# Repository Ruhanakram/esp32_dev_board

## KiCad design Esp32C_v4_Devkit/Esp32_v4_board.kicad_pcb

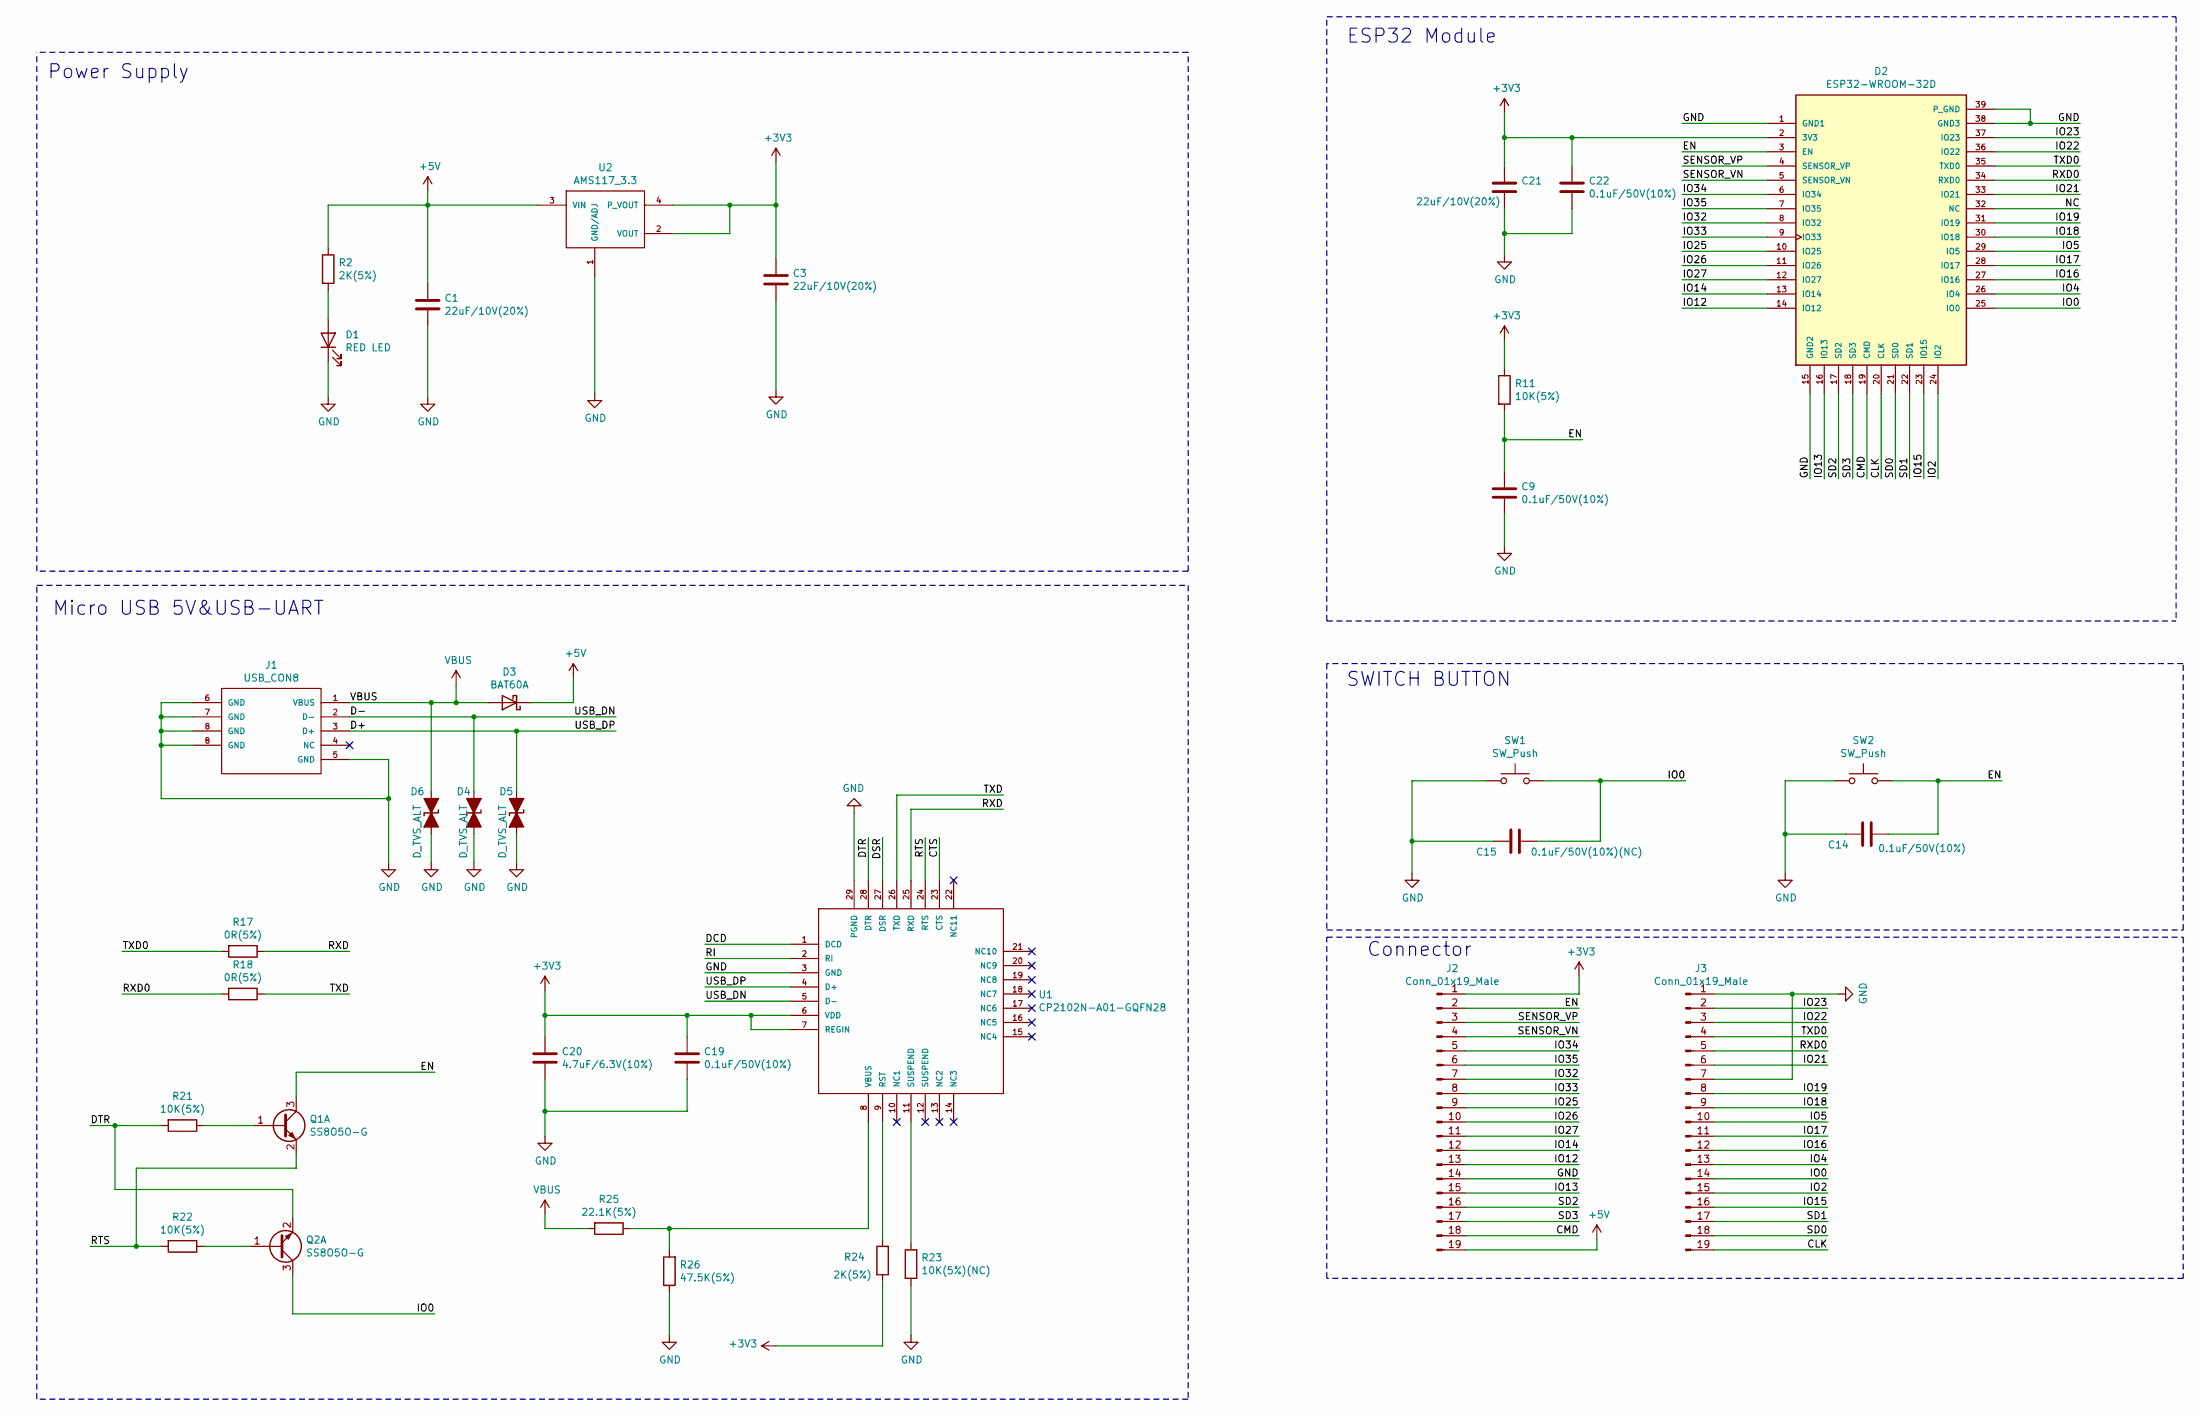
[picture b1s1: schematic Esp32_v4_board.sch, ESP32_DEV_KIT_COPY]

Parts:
C1, C3, C21: 22uF/10V(20%); C_0603_1608Metric
C9, C14, C19, C22: 0.1uF/50V(10%); C_0402_1005Metric
C15: 0.1uF/50V(10%)(NC); C_0603_1608Metric
C20: 4.7uF/6.3V(10%); C_0402_1005Metric
D1: RED LED; LED_0603_1608Metric
D2: ESP32-WROOM-32D; esp32_wroom_32e; PARTREV 1.9
D3: BAT60A; D_SOD-323
D4, D5, D6: D_TVS_ALT; D_SOD-523
J1: USB_CON8; Micro_usb_connector_4_THT_pads
J2, J3: Conn_01x19_Male; PinHeader_1x19_P2.54mm_Vertical
Q1, Q2: SS8O5O-G; TSOT-23
R2, R24: 2K(5%); R_0402_1005Metric
R11, R21, R22: 10K(5%); R_0402_1005Metric
R17, R18: 0R(5%); R_0402_1005Metric
R23: 10K(5%)(NC); R_0402_1005Metric
R25: 22.1K(5%); R_0402_1005Metric
R26: 47.5K(5%); R_0402_1005Metric
SW1, SW2: SW_Push; SW_SPST_B3U-1000P
U1: CP2102N-A01-GQFN28; QFN-28-1EP_5x5mm_P0.5mm_EP3.35x3.35mm
U2: AMS117_3.3; SOT-223

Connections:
+3V3: C3.1, C19.1, C20.1, C21.1, C22.1, D2.2 (3V3), J2.1, R11.1, R24.1, U1.6 (VDD), U1.7 (REGIN), U2.2 (VOUT), U2.4 (P_VOUT)
+5V: C1.1, D3.1 (K), J2.19, R2.1, U2.3 (VIN)
/CLK: D2.20 (CLK), J3.19
/CMD: D2.19 (CMD), J2.18
/CTS: U1.23 (CTS)
/D+: D5.2 (A2), J1.3 (D+), U1.4 (D+)
/D-: D4.2 (A2), J1.2 (D-), U1.5 (D-)
/DCD: U1.1 (DCD)
/DSR: U1.27 (DSR)
/DTR: Q2.2 (E1), R21.2, U1.28 (DTR)
/EN: C9.1, C14.2, D2.3 (EN), J2.2, Q1.3 (C1), R11.2, SW2.2
/IO0: C15.2, D2.25 (IO0), J3.14, Q2.3 (C1), SW1.2
/IO2: D2.24 (IO2), J3.15
/IO4: D2.26 (IO4), J3.13
/IO5: D2.29 (IO5), J3.10
/IO12: D2.14 (IO12), J2.13
/IO13: D2.16 (IO13), J2.15
/IO14: D2.13 (IO14), J2.12
/IO15: D2.23 (IO15), J3.16
/IO16: D2.27 (IO16), J3.12
/IO17: D2.28 (IO17), J3.11
/IO18: D2.30 (IO18), J3.9
/IO19: D2.31 (IO19), J3.8
/IO21: D2.33 (IO21), J3.6
/IO22: D2.36 (IO22), J3.3
/IO23: D2.37 (IO23), J3.2
/IO25: D2.10 (IO25), J2.9
/IO26: D2.11 (IO26), J2.10
/IO27: D2.12 (IO27), J2.11
/IO32: D2.8 (IO32), J2.7
/IO33: D2.9 (IO33), J2.8
/IO34: D2.6 (IO34), J2.5
/IO35: D2.7 (IO35), J2.6
/NC: D2.32 (NC)
/RI: U1.2 (RI)
/RTS: Q1.2 (E1), R22.2, U1.24 (RTS)
/RXD: R17.1, U1.25 (RXD)
/RXD0: D2.34 (RXD0), J3.5, R18.2
/SD0: D2.21 (SD0), J3.18
/SD1: D2.22 (SD1), J3.17
/SD2: D2.17 (SD2), J2.16
/SD3: D2.18 (SD3), J2.17
/SENSOR_VN: D2.5 (SENSOR_VN), J2.4
/SENSOR_VP: D2.4 (SENSOR_VP), J2.3
/TXD: R18.1, U1.26 (TXD)
/TXD0: D2.35 (TXD0), J3.4, R17.2
GND: C1.2, C3.2, C9.2, C14.1, C15.1, C19.2, C20.2, C21.2, C22.2, D1.1 (K), D2.1 (GND1), D2.15 (GND2), D2.38 (GND3), D2.39 (P_GND), D4.1 (A1), D5.1 (A1), D6.1 (A1), J1.5 (GND), J1.6 (GND), J1.7 (GND), J1.8 (GND), J2.14, J3.1, J3.7, R23.1, R26.1, SW1.1, SW2.1, U1.3 (GND), U1.29 (PGND), U2.1 (GND/ADJ)
unnamed: D1.2 (A), R2.2
unnamed: Q1.1 (B1), R21.1
unnamed: Q2.1 (B1), R22.1
unnamed: R23.2, U1.11 (SUSPEND)
unnamed: R24.2, U1.9 (RST)
unnamed: R25.1, R26.2, U1.8 (VBUS)
VBUS: D3.2 (A), D6.2 (A2), J1.1 (VBUS), R25.2

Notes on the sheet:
Power Supply
Micro USB 5V&USB-UART
ESP32 Module
SWITCH BUTTON
Connector

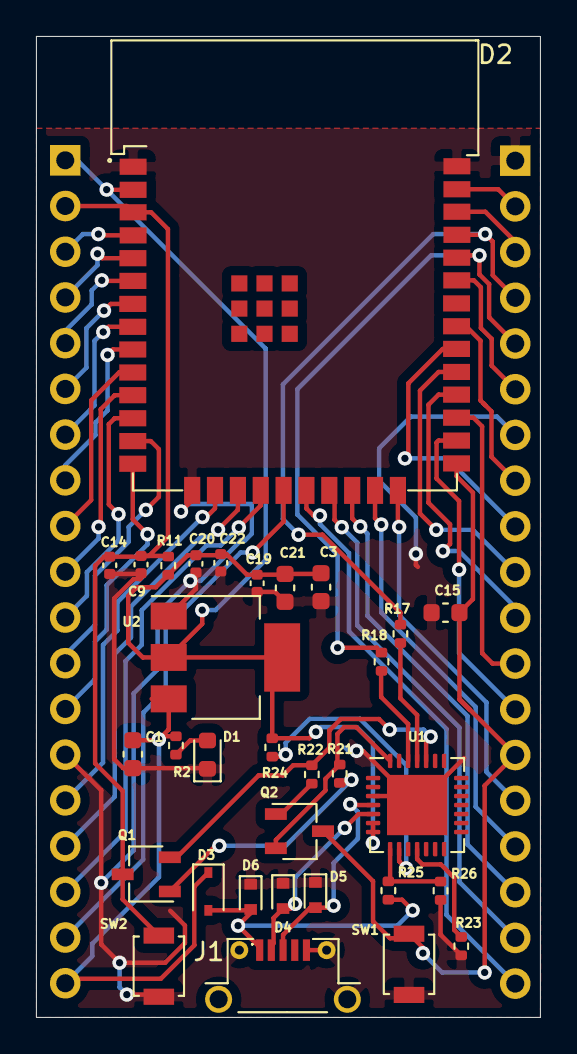
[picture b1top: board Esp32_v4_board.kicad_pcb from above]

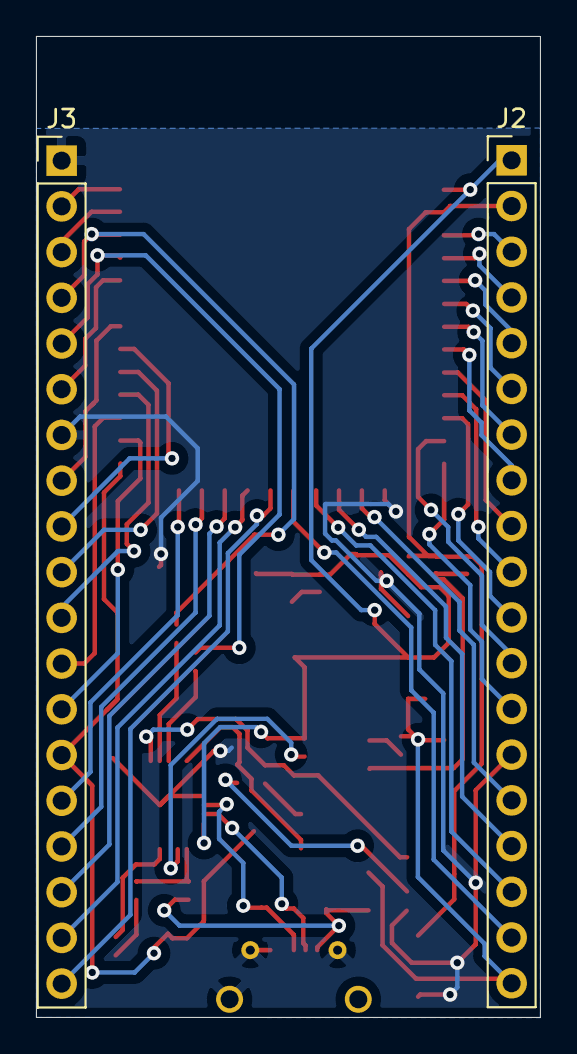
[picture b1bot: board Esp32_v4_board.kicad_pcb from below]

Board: 2 copper layers, 28.0 x 54.5 mm, 34 parts (2 on the bottom side), 49 nets.

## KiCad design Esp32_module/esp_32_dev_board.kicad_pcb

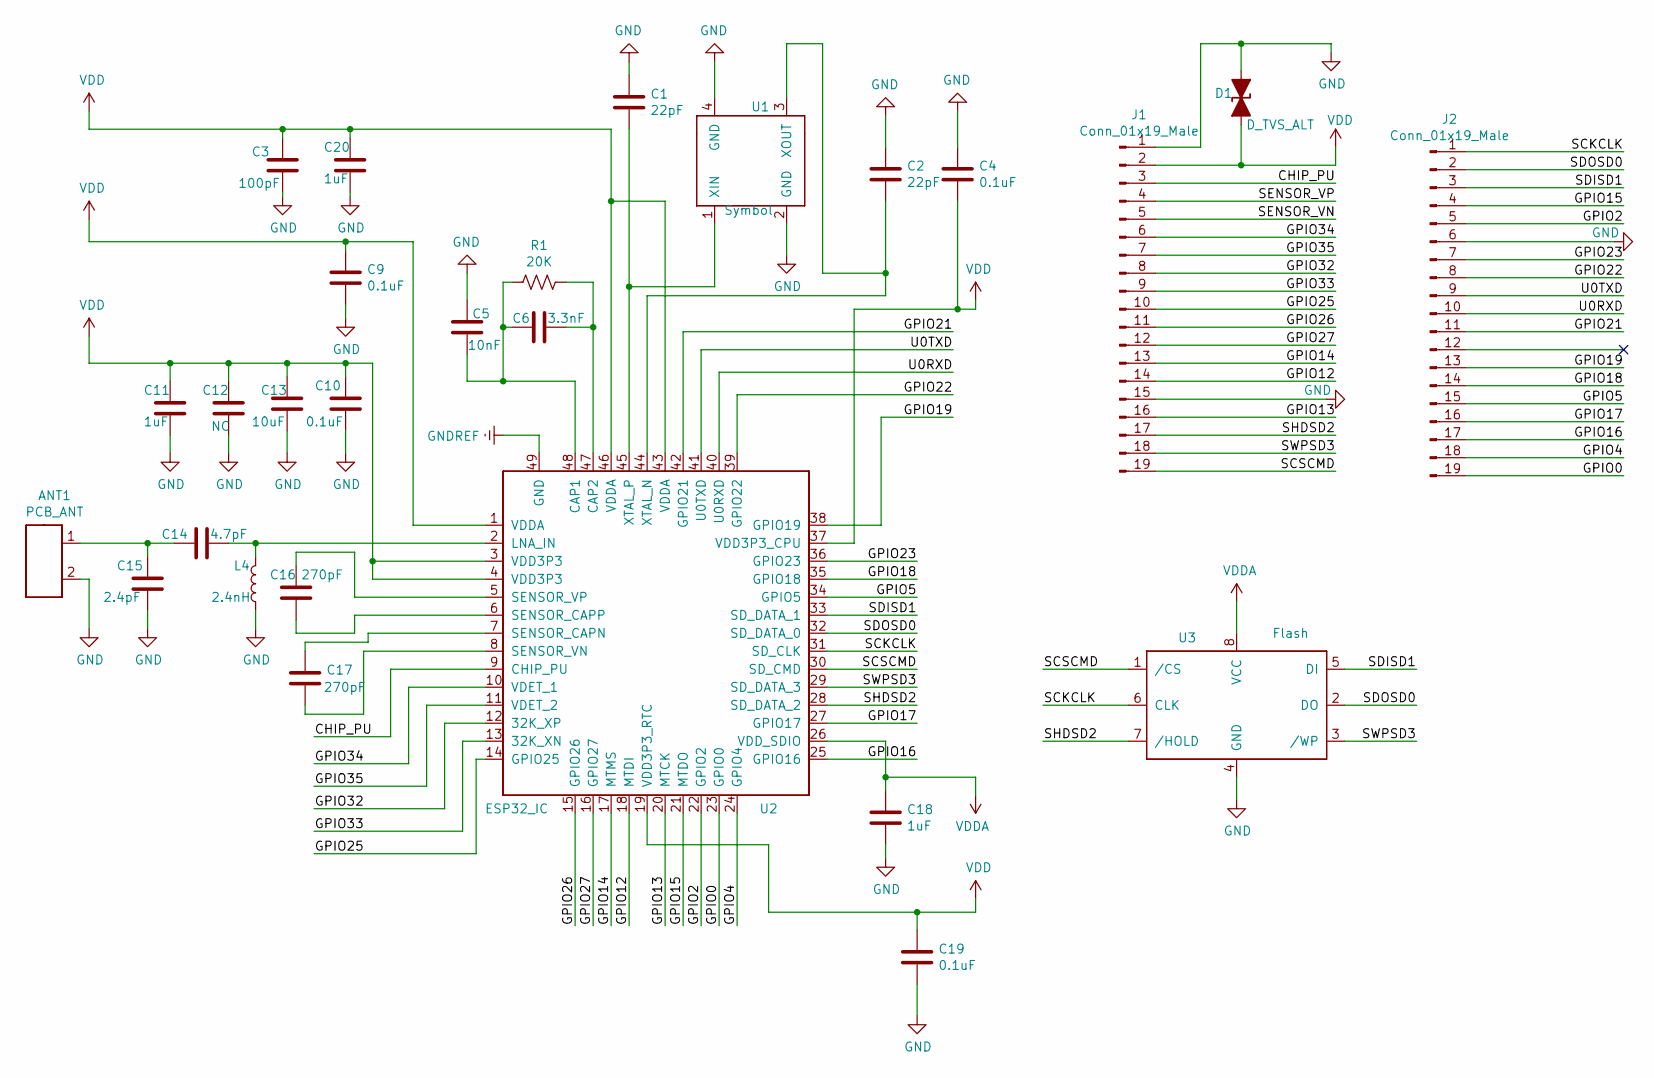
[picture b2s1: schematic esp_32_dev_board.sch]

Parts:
ANT1: PCB_ANT; Texas_SWRA117D_2.4GHz_Right
C1, C2: 22pF; C_01005_0402Metric
C3: 100pF; C_01005_0402Metric
C4, C9, C10, C19: 0.1uF; C_01005_0402Metric
C5: 10nF; C_01005_0402Metric
C6: 3.3nF; C_01005_0402Metric
C11, C18, C20: 1uF; C_01005_0402Metric
C12: NC; R_0603_1608Metric
C13: 10uF; C_0201_0603Metric
C14: 4.7pF; C14_GRM1555C1H4R7BA01D
C15: 2.4pF; C15_GRM1555C1H2R4CA01D
C16, C17: 270pF; C_01005_0402Metric
D1: D_TVS_ALT; DIODFN2_98X58X50L26X51N
J1, J2: Conn_01x19_Male; PinHeader_1x19_P2.54mm_Vertical
L4: 2.4nH; L4_LQP15MN2N4B02D
R1: 20K; R_0402_1005Metric
U1: Symbol; Crystal_SMD_3225-4Pin_3.2x2.5mm_HandSoldering
U2: ESP32_IC; QFN35P500X500X90-49N
U3: Flash; GD25Q32

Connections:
/CHIP_PU: J1.3, U2.9 (CHIP_PU)
/GPIO0: J2.19, U2.23 (GPIO0)
/GPIO2: J2.5, U2.22 (GPIO2)
/GPIO4: J2.18, U2.24 (GPIO4)
/GPIO5: J2.15, U2.34 (GPIO5)
/GPIO12: J1.14, U2.18 (MTDI)
/GPIO13: J1.16, U2.20 (MTCK)
/GPIO14: J1.13, U2.17 (MTMS)
/GPIO15: J2.4, U2.21 (MTDO)
/GPIO16: J2.17, U2.25 (GPIO16)
/GPIO17: J2.16, U2.27 (GPIO17)
/GPIO18: J2.14, U2.35 (GPIO18)
/GPIO19: J2.13, U2.38 (GPIO19)
/GPIO21: J2.11, U2.42 (GPIO21)
/GPIO22: J2.8, U2.39 (GPIO22)
/GPIO23: J2.7, U2.36 (GPIO23)
/GPIO25: J1.10, U2.14 (GPIO25)
/GPIO26: J1.11, U2.15 (GPIO26)
/GPIO27: J1.12, U2.16 (GPIO27)
/GPIO32: J1.8, U2.12 (32K_XP)
/GPIO33: J1.9, U2.13 (32K_XN)
/GPIO34: J1.6, U2.10 (VDET_1)
/GPIO35: J1.7, U2.11 (VDET_2)
/SCKCLK: J2.1, U2.31 (SD_CLK), U3.6 (CLK)
/SCSCMD: J1.19, U2.30 (SD_CMD), U3.1 (/CS)
/SDISD1: J2.3, U2.33 (SD_DATA_1), U3.5 (DI)
/SDOSD0: J2.2, U2.32 (SD_DATA_0), U3.2 (DO)
/SENSOR_VN: J1.5
/SENSOR_VP: J1.4
/SHDSD2: J1.17, U2.28 (SD_DATA_2), U3.7 (/HOLD)
/SWPSD3: J1.18, U2.29 (SD_DATA_3), U3.3 (/WP)
/U0RXD: J2.10, U2.40 (U0RXD)
/U0TXD: J2.9, U2.41 (U0TXD)
GND: ANT1.2, C1.1, C2.1, C3.2, C4.1, C5.1, C9.2, C10.2, C11.2, C12.2, C13.2, C15.1, C18.1, C19.1, C20.2, D1.1 (A1), J1.1, J1.15, J2.6, L4.1, U1.2 (GND), U1.4 (GND), U3.4 (GND)
GNDREF: U2.49 (GND)
unnamed: ANT1.1, C14.2, C15.2
unnamed: C1.2, U1.1 (XIN), U2.45 (XTAL_P)
unnamed: C2.2, U1.3 (XOUT), U2.44 (XTAL_N)
unnamed: C5.2, C6.1, R1.2, U2.48 (CAP1)
unnamed: C6.2, R1.1, U2.47 (CAP2)
unnamed: C14.1, L4.2, U2.2 (LNA_IN)
unnamed: C16.1, U2.6 (SENSOR_CAPP)
unnamed: C16.2, U2.5 (SENSOR_VP)
unnamed: C17.1, U2.8 (SENSOR_VN)
unnamed: C17.2, U2.7 (SENSOR_CAPN)
VDD: C3.1, C4.2, C9.1, C10.1, C11.1, C12.1, C13.1, C19.2, C20.1, D1.2 (A2), J1.2, U2.1 (VDDA), U2.3 (VDD3P3), U2.4 (VDD3P3), U2.19 (VDD3P3_RTC), U2.37 (VDD3P3_CPU), U2.43 (VDDA), U2.46 (VDDA)
VDDA: C18.2, U2.26 (VDD_SDIO), U3.8 (VCC)

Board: 2 copper layers, 27 parts (0 on the bottom side), 44 nets, no tracks yet.

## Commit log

2021-03-19 second commit included some footprins
2021-04-01 complete schematics
2021-04-01 New project first commit
2021-04-23 Routing and components placement
2021-04-27 Updated board
2021-04-29 Updated routing corrections
2021-05-02 symbol updated
